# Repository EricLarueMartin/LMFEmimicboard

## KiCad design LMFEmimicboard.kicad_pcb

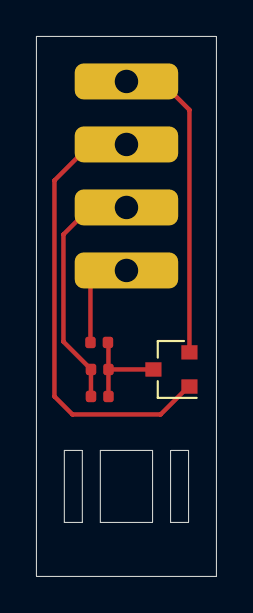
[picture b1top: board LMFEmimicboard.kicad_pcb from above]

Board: 2 copper layers, 10.0 x 30.0 mm, 8 parts (0 on the bottom side), 5 nets.

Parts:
C1, C2: C; R_0402_1005Metric
J1: D; Pin_D1.3mm_L5.75mmW2.0mm
J2: S; Pin_D1.3mm_L5.75mmW2.0mm
J3: F; Pin_D1.3mm_L5.75mmW2.0mm
J4: P; Pin_D1.3mm_L5.75mmW2.0mm
Q1: Q_NJFET_SDG; SOT-23
R1: R; R_0402_1005Metric

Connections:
GND: J2.1, Q1.1
unnamed: C1.1, C2.1, Q1.3, R1.1
unnamed: C1.2, J3.1, J3.2, R1.2
unnamed: C2.2, J4.1
unnamed: J1.1, Q1.2

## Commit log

2021-05-17 Generated .pdf of layout.
2021-05-18 Changed values to match the LMFE.
